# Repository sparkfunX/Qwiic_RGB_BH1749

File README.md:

SparkFun RGB Sensor (Qwiic) - BH1749NUC
========================================

[*SparkX RGB Sensor (Qwiic) - BH1749NUC (SPX-14733)*](https://www.sparkfun.com/products/14733)

Need to autonomously monitor for that specific color value? Want to hone in on that magenta ball? Or follow that aquamarine line? The BH1749NUC-based Qwiic RGB Sensor is here for all of your <span style="color:red">red</span>, <span style="color:green">green</span>, <span style="color:blue">blue</span>, and <span style="color:darkred">infrared</span> color-sensing needs.

The **BH1749NUC** features an I<sup>2</sup>C interface and a programmable interrupt output. It senses red, green, blue, and infrared in its field-of-view, then reports them as a 16-bit value. Additionally, it features programmable IR and RGB gains and a variable measurement rate. 

Also included on the breakout are individually-controllable white, red, green, and blue LEDs. The LEDs are managed with a **PCA9536** 4-channel I/O I<sup>2</sup>C expander. We've got a library for that too!

Check out the documents section for a pair of Arduino libraries -- for both the [BH1749NUC](https://github.com/sparkfun/SparkFun_BH1749NUC_Arduino_Library) and [PCA9536](https://github.com/sparkfun/SparkFun_PCA9536_Arduino_Library) IC's -- and a handful of examples to help get you started.

The Qwiic RGB Sensor uses our simple [Qwiic](https://www.sparkfun.com/qwiic) interface, so it requires no voltage translation and no figuring out which pin is SDA or SCL; just plug it in and go! As with any Qwiic board, this product includes a pair of Qwiic connectors to support a chain of multiple sensors.

SparkFun labored with love to create this code. Feel like supporting open source hardware? 
Buy a [breakout board](https://www.sparkfun.com/products/14733) from SparkFun!

Repository Contents
-------------------

* **/Documents** - Datasheets
* **/Hardware** - Eagle design files (.brd, .sch)

License Information
-------------------

This product is _**open source**_! 

If you have any questions or concerns on licensing, please contact techsupport@sparkfun.com.

Please use, reuse, and modify these files as you see fit. Please maintain attribution to SparkFun Electronics and release any derivative under the same license.

Distributed as-is; no warranty is given.

- Your friends at SparkFun.

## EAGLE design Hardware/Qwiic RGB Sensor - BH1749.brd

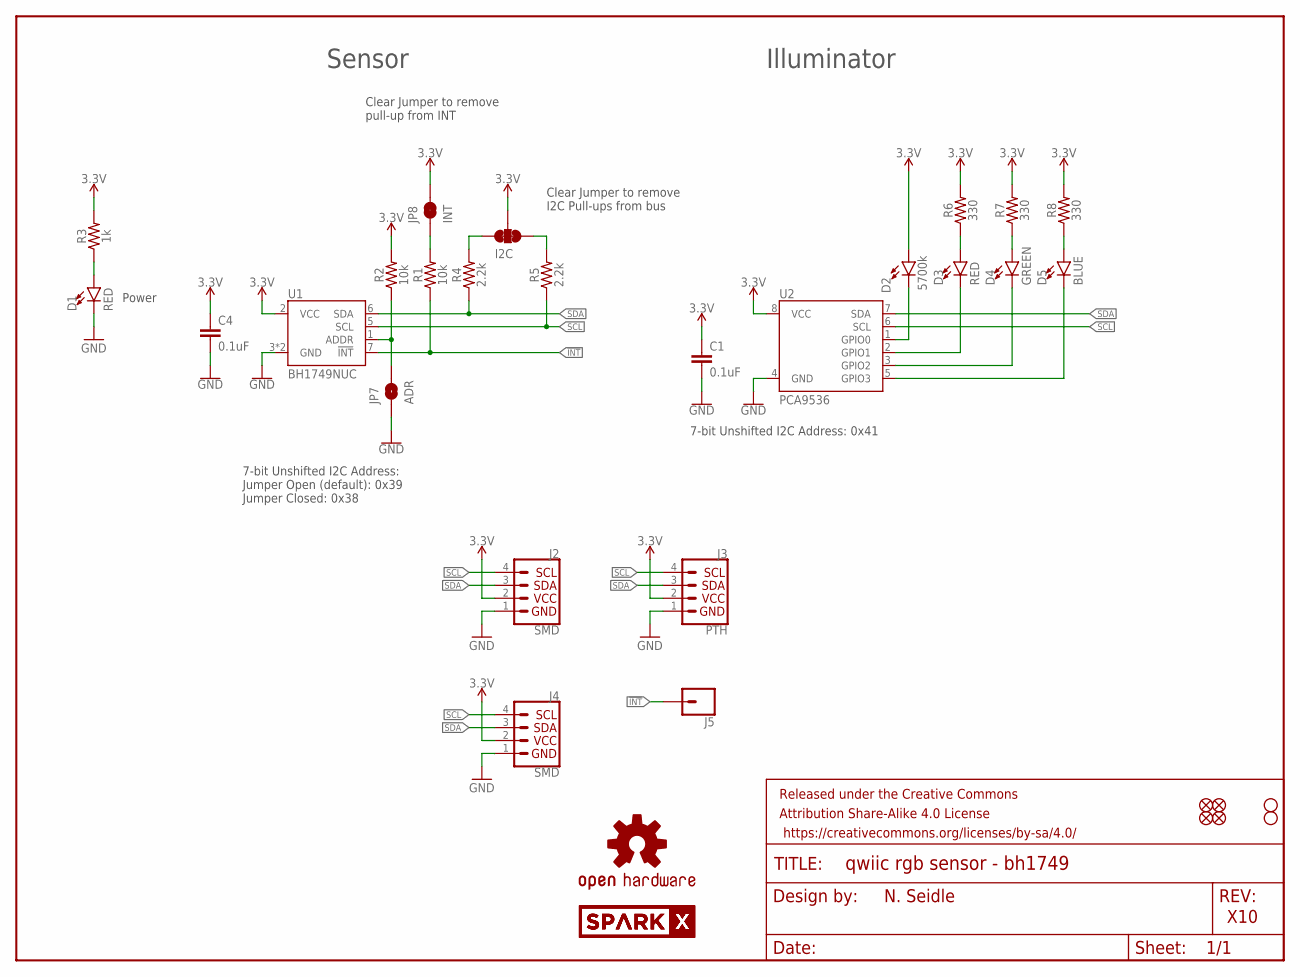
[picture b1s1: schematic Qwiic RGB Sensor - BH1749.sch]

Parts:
C1, C4: 0.1uF; 0603
D1, D3: RED; LED-0603
D2: 5700k; SUPER_BRIGHT_SMD_LED_1206
D4: GREEN; LED-0603
D5: BLUE; LED-0603
FRAME1: FRAME-LETTER; CREATIVE_COMMONS
I2C: JUMPER-SMT_3_2-NC_TRACE_SILK; SMT-JUMPER_3_2-NC_TRACE_SILK
J2, J4: SMD; 1X04_1MM_RA
J3: PTH; 1X04_NO_SILK
J5: CONN_01PTH_NO_SILK_YES_STOP; 1X01_NO_SILK
JP1, JP2, JP5, JP6: FIDUCIALUFIDUCIAL; MICRO-FIDUCIAL
JP3, JP4: STAND-OFF
JP7: ADR; SMT-JUMPER_2_NO_SILK
JP8: INT; SMT-JUMPER_2_NC_TRACE_SILK
LOGO1: OSHW-LOGOMINI; OSHW-LOGO-MINI
R1, R2: 10k; 0603
R3: 1k; 0603
R4, R5: 2.2k; 0603
R6, R7, R8: 330; 0603
U1: BH1749NUC
U2: PCA9536; MSOP8
U$1, U$2: SPARKX-LOGO4; SPARKX-MEDIUM

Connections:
3.3V: C1.1, C4.1, D2.A, I2C.2, J2.2 (VCC), J3.2 (VCC), J4.2 (VCC), JP8.2, R2.2, R3.2, R6.2, R7.2, R8.2, U1.2 (VCC), U2.8 (VCC)
!INT: J5.1, R1.1, U1.7 (!INT)
ADR: JP7.2, R2.1, U1.1 (ADDR)
GND: C1.2, C4.2, D1.C, J2.1 (GND), J3.1 (GND), J4.1 (GND), JP7.1, U1.3 (GND), U1.4 (GND), U2.4 (GND)
unnamed: I2C.1, R5.2
unnamed: I2C.3, R4.2
unnamed: D1.A, R3.1
unnamed: JP8.1, R1.2
unnamed: D3.C, U2.2 (GPIO1)
unnamed: D4.C, U2.3 (GPIO2)
unnamed: D5.C, U2.5 (GPIO3)
unnamed: D3.A, R6.1
unnamed: D4.A, R7.1
unnamed: D2.C, U2.1 (GPIO0)
unnamed: D5.A, R8.1
SCL: J2.4 (SCL), J3.4 (SCL), J4.4 (SCL), R5.1, U1.5 (SCL), U2.6 (SCL)
SDA: J2.3 (SDA), J3.3 (SDA), J4.3 (SDA), R4.1, U1.6 (SDA), U2.7 (SDA)

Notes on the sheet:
N. Seidle
X10
7-bit Unshifted I2C Address: Jumper Open (default): 0x39 Jumper Closed: 0x38
Clear Jumper to remove I2C Pull-ups from bus
Clear Jumper to remove pull-up from INT
Power
7-bit Unshifted I2C Address: 0x41
Sensor
Illuminator

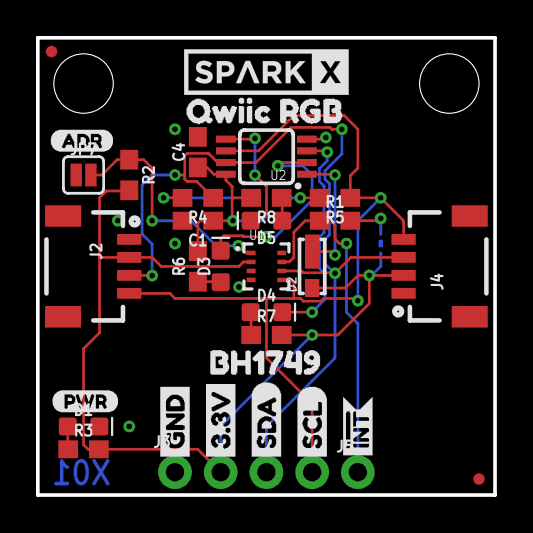
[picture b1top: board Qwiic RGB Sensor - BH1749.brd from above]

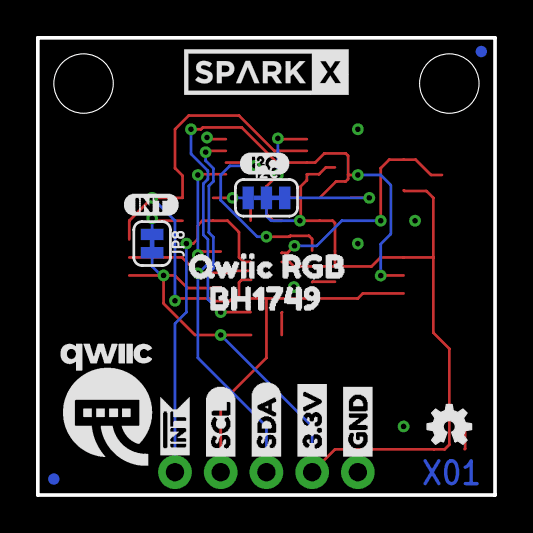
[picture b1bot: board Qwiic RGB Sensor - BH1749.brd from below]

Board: 2 copper layers, 25.4 x 25.4 mm, 53 parts (16 on the bottom side), 17 nets.

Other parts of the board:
U$3, U$22: GND1
U$4, U$21: 3#3V2
U$5, U$27: SDA8
U$6, U$26: SCL9
U$7, U$9: INT#-[<
U$8: QWIIC-LOGO-MEDIUM
U$10: I_SUPER2_C-()-03
U$11, U$13: BH17493
U$12, U$24: QWIIC_RGB2
U$16: PWR-()-03
U$17: ADR-()-03
U$20: INT0

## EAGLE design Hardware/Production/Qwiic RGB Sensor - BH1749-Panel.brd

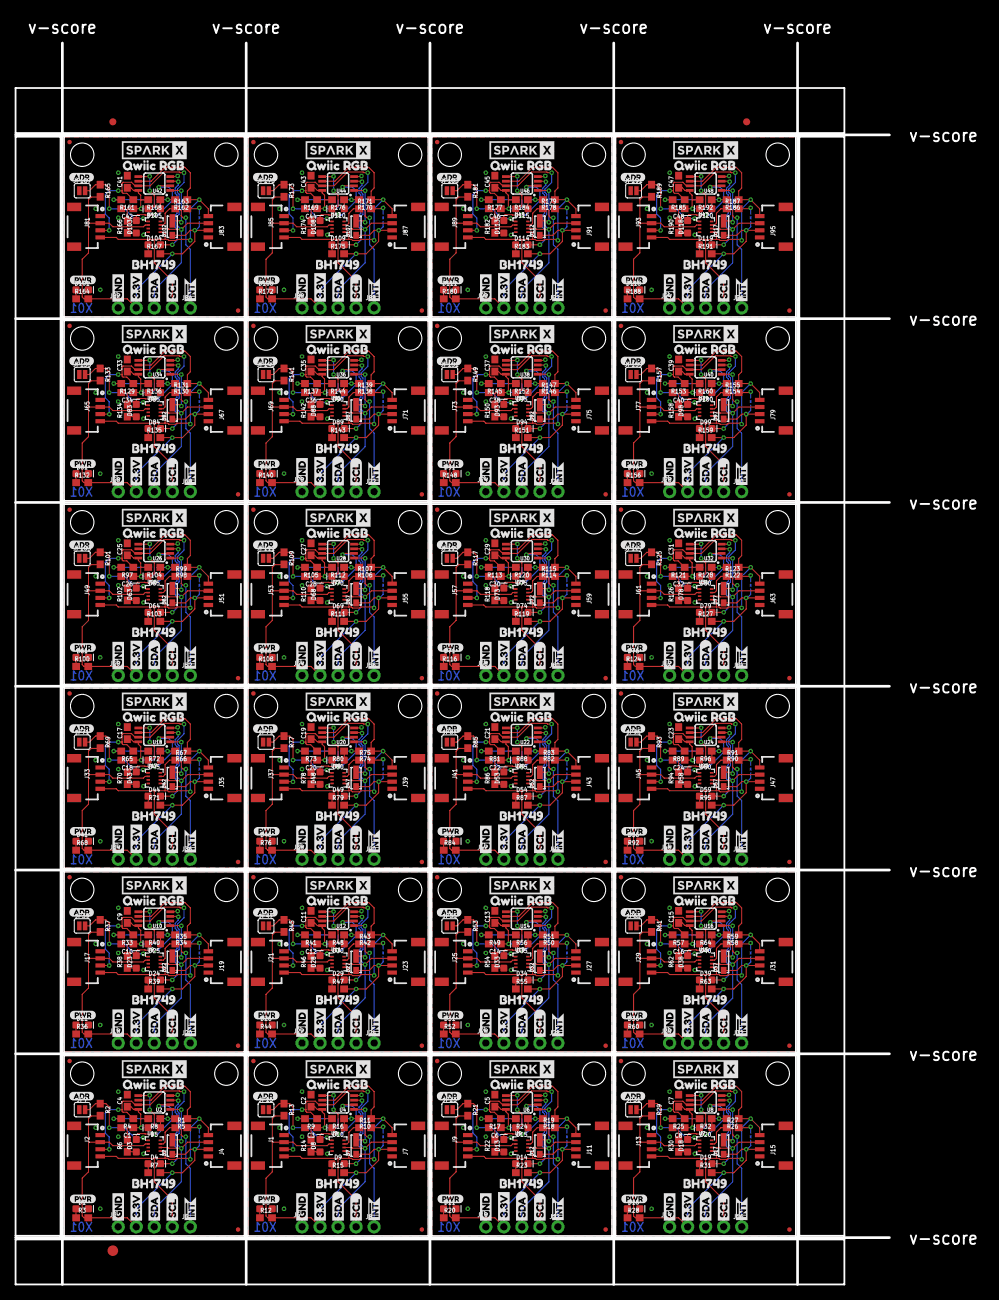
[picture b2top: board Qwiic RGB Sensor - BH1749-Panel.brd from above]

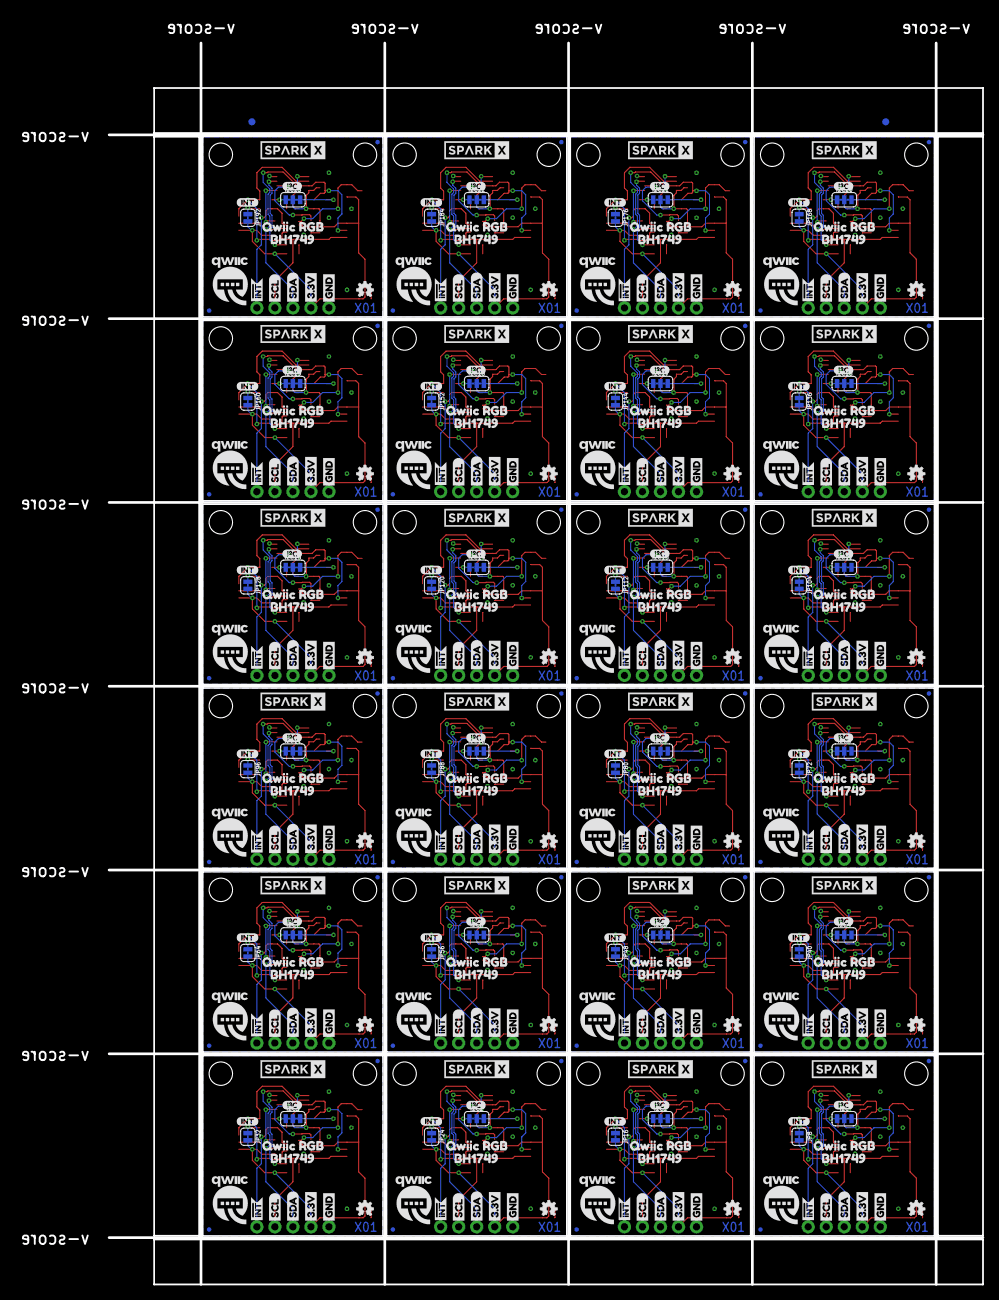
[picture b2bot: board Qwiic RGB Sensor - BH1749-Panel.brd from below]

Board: 2 copper layers, 123.2 x 175.0 mm, 1253 parts (386 on the bottom side), 408 nets.

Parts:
C1, C2, C3, C4, C5, C6, C7, C8, C9, C10, C11, C12, C13, C14, C15, C16, C17, C18, C19, C20, C21, C22, C23, C24, C25, C26, C27, C28, C29, C30, C31, C32, C33, C34, C35, C36, C37, C38, C39, C40, C41, C42, C43, C44, C45, C46, C47, C48: 0.1uF; 0603
D1, D3, D6, D8, D11, D13, D16, D18, D21, D23, D26, D28, D31, D33, D36, D38, D41, D43, D46, D48, D51, D53, D56, D58, D61, D63, D66, D68, D71, D73, D76, D78, D81, D83, D86, D88, D91, D93, D96, D98, D101, D103, D106, D108, D111, D113, D116, D118: RED; LED-0603
D2, D7, D12, D17, D22, D27, D32, D37, D42, D47, D52, D57, D62, D67, D72, D77, D82, D87, D92, D97, D102, D107, D112, D117: 5700k; SUPER_BRIGHT_SMD_LED_1206
D4, D9, D14, D19, D24, D29, D34, D39, D44, D49, D54, D59, D64, D69, D74, D79, D84, D89, D94, D99, D104, D109, D114, D119: GREEN; LED-0603
D5, D10, D15, D20, D25, D30, D35, D40, D45, D50, D55, D60, D65, D70, D75, D80, D85, D90, D95, D100, D105, D110, D115, D120: BLUE; LED-0603
E$1, E$2, E$3, E$4: FIDUCIAL-1X2
E$5: FIDUCIAL-1.5X3
I2C, I2C1, I2C2, I2C3, I2C4, I2C5, I2C6, I2C7, I2C8, I2C9, I2C10, I2C11, I2C12, I2C13, I2C14, I2C15, I2C16, I2C17, I2C18, I2C19, I2C20, I2C21, I2C22, I2C23: SMT-JUMPER_3_2-NC_TRACE_SILK
J1, J2, J4, J7, J9, J11, J13, J15, J17, J19, J21, J23, J25, J27, J29, J31, J33, J35, J37, J39, J41, J43, J45, J47, J49, J51, J53, J55, J57, J59, J61, J63, J65, J67, J69, J71, J73, J75, J77, J79, J81, J83, J85, J87, J89, J91, J93, J95: SMD; 1X04_1MM_RA
J3, J6, J10, J14, J18, J22, J26, J30, J34, J38, J42, J46, J50, J54, J58, J62, J66, J70, J74, J78, J82, J86, J90, J94: PTH; 1X04_NO_SILK
J5, J8, J12, J16, J20, J24, J28, J32, J36, J40, J44, J48, J52, J56, J60, J64, J68, J72, J76, J80, J84, J88, J92, J96: 1X01_NO_SILK
JP1, JP2, JP5, JP6, JP11, JP12, JP13, JP14, JP19, JP20, JP21, JP22, JP27, JP28, JP29, JP30, JP35, JP36, JP37, JP38, JP43, JP44, JP45, JP46, JP51, JP52, JP53, JP54, JP59, JP60, JP61, JP62, JP67, JP68, JP69, JP70, JP75, JP76, JP77, JP78, JP83, JP84, JP85, JP86, JP91, JP92, JP93, JP94, JP99, JP100, JP101, JP102, JP107, JP108, JP109, JP110, JP115, JP116, JP117, JP118, JP123, JP124, JP125, JP126, JP131, JP132, JP133, JP134, JP139, JP140, JP141, JP142, JP147, JP148, JP149, JP150, JP155, JP156, JP157, JP158, JP163, JP164, JP165, JP166, JP171, JP172, JP173, JP174, JP179, JP180, JP181, JP182, JP187, JP188, JP189, JP190: FIDUCIALUFIDUCIAL; MICRO-FIDUCIAL
JP3, JP4, JP9, JP10, JP17, JP18, JP25, JP26, JP33, JP34, JP41, JP42, JP49, JP50, JP57, JP58, JP65, JP66, JP73, JP74, JP81, JP82, JP89, JP90, JP97, JP98, JP105, JP106, JP113, JP114, JP121, JP122, JP129, JP130, JP137, JP138, JP145, JP146, JP153, JP154, JP161, JP162, JP169, JP170, JP177, JP178, JP185, JP186: STAND-OFF
JP7, JP15, JP23, JP31, JP39, JP47, JP55, JP63, JP71, JP79, JP87, JP95, JP103, JP111, JP119, JP127, JP135, JP143, JP151, JP159, JP167, JP175, JP183, JP191: ADR; SMT-JUMPER_2_NO_SILK
JP8, JP16, JP24, JP32, JP40, JP48, JP56, JP64, JP72, JP80, JP88, JP96, JP104, JP112, JP120, JP128, JP136, JP144, JP152, JP160, JP168, JP176, JP184, JP192: INT; SMT-JUMPER_2_NC_TRACE_SILK
LOGO1, LOGO2, LOGO3, LOGO4, LOGO5, LOGO6, LOGO7, LOGO8, LOGO9, LOGO10, LOGO11, LOGO12, LOGO13, LOGO14, LOGO15, LOGO16, LOGO17, LOGO18, LOGO19, LOGO20, LOGO21, LOGO22, LOGO23, LOGO24: OSHW-LOGOMINI; OSHW-LOGO-MINI
R1, R2, R11, R13, R19, R21, R27, R29, R35, R37, R43, R45, R51, R53, R59, R61, R67, R69, R75, R77, R83, R85, R91, R93, R99, R101, R107, R109, R115, R117, R123, R125, R131, R133, R139, R141, R147, R149, R155, R157, R163, R165, R171, R173, R179, R181, R187, R189: 10k; 0603
R3, R12, R20, R28, R36, R44, R52, R60, R68, R76, R84, R92, R100, R108, R116, R124, R132, R140, R148, R156, R164, R172, R180, R188: 1k; 0603
R4, R5, R9, R10, R17, R18, R25, R26, R33, R34, R41, R42, R49, R50, R57, R58, R65, R66, R73, R74, R81, R82, R89, R90, R97, R98, R105, R106, R113, R114, R121, R122, R129, R130, R137, R138, R145, R146, R153, R154, R161, R162, R169, R170, R177, R178, R185, R186: 2.2k; 0603
R6, R7, R8, R14, R15, R16, R22, R23, R24, R30, R31, R32, R38, R39, R40, R46, R47, R48, R54, R55, R56, R62, R63, R64, R70, R71, R72, R78, R79, R80, R86, R87, R88, R94, R95, R96, R102, R103, R104, R110, R111, R112, R118, R119, R120, R126, R127, R128, R134, R135, R136, R142, R143, R144, R150, R151, R152, R158, R159, R160, R166, R167, R168, R174, R175, R176, R182, R183, R184, R190, R191, R192: 330; 0603
U1, U3, U5, U7, U9, U11, U13, U15, U17, U19, U21, U23, U25, U27, U29, U31, U33, U35, U37, U39, U41, U43, U45, U47: BH1749NUC
U2, U4, U6, U8, U10, U12, U14, U16, U18, U20, U22, U24, U26, U28, U30, U32, U34, U36, U38, U40, U42, U44, U46, U48: PCA9536; MSOP8
U$1, U$2, U$14, U$15, U$43, U$44, U$64, U$65, U$85, U$86, U$106, U$107, U$127, U$128, U$148, U$149, U$169, U$170, U$190, U$191, U$211, U$212, U$232, U$233, U$253, U$254, U$274, U$275, U$295, U$296, U$316, U$317, U$337, U$338, U$358, U$359, U$379, U$380, U$400, U$401, U$421, U$422, U$442, U$443, U$463, U$464, U$484, U$485: SPARKX-LOGO4; SPARKX-MEDIUM
U$3, U$19, U$22, U$28, U$46, U$49, U$67, U$70, U$88, U$91, U$109, U$112, U$130, U$133, U$151, U$154, U$172, U$175, U$193, U$196, U$214, U$217, U$235, U$238, U$256, U$259, U$277, U$280, U$298, U$301, U$319, U$322, U$340, U$343, U$361, U$364, U$382, U$385, U$403, U$406, U$424, U$427, U$445, U$448, U$466, U$469, U$487, U$490: GND1
U$4, U$18, U$21, U$29, U$45, U$50, U$66, U$71, U$87, U$92, U$108, U$113, U$129, U$134, U$150, U$155, U$171, U$176, U$192, U$197, U$213, U$218, U$234, U$239, U$255, U$260, U$276, U$281, U$297, U$302, U$318, U$323, U$339, U$344, U$360, U$365, U$381, U$386, U$402, U$407, U$423, U$428, U$444, U$449, U$465, U$470, U$486, U$491: 3#3V2
U$5, U$25, U$27, U$30, U$48, U$51, U$69, U$72, U$90, U$93, U$111, U$114, U$132, U$135, U$153, U$156, U$174, U$177, U$195, U$198, U$216, U$219, U$237, U$240, U$258, U$261, U$279, U$282, U$300, U$303, U$321, U$324, U$342, U$345, U$363, U$366, U$384, U$387, U$405, U$408, U$426, U$429, U$447, U$450, U$468, U$471, U$489, U$492: SDA8
U$6, U$23, U$26, U$31, U$47, U$52, U$68, U$73, U$89, U$94, U$110, U$115, U$131, U$136, U$152, U$157, U$173, U$178, U$194, U$199, U$215, U$220, U$236, U$241, U$257, U$262, U$278, U$283, U$299, U$304, U$320, U$325, U$341, U$346, U$362, U$367, U$383, U$388, U$404, U$409, U$425, U$430, U$446, U$451, U$467, U$472, U$488, U$493: SCL9
U$7, U$9, U$33, U$34, U$54, U$55, U$75, U$76, U$96, U$97, U$117, U$118, U$138, U$139, U$159, U$160, U$180, U$181, U$201, U$202, U$222, U$223, U$243, U$244, U$264, U$265, U$285, U$286, U$306, U$307, U$327, U$328, U$348, U$349, U$369, U$370, U$390, U$391, U$411, U$412, U$432, U$433, U$453, U$454, U$474, U$475, U$495, U$496: INT#-[<
U$8, U$32, U$53, U$74, U$95, U$116, U$137, U$158, U$179, U$200, U$221, U$242, U$263, U$284, U$305, U$326, U$347, U$368, U$389, U$410, U$431, U$452, U$473, U$494: QWIIC-LOGO-MEDIUM
U$10, U$37, U$58, U$79, U$100, U$121, U$142, U$163, U$184, U$205, U$226, U$247, U$268, U$289, U$310, U$331, U$352, U$373, U$394, U$415, U$436, U$457, U$478, U$499: I_SUPER2_C-()-03
U$11, U$13, U$38, U$42, U$59, U$63, U$80, U$84, U$101, U$105, U$122, U$126, U$143, U$147, U$164, U$168, U$185, U$189, U$206, U$210, U$227, U$231, U$248, U$252, U$269, U$273, U$290, U$294, U$311, U$315, U$332, U$336, U$353, U$357, U$374, U$378, U$395, U$399, U$416, U$420, U$437, U$441, U$458, U$462, U$479, U$483, U$500, U$504: BH17493
U$12, U$24, U$40, U$41, U$61, U$62, U$82, U$83, U$103, U$104, U$124, U$125, U$145, U$146, U$166, U$167, U$187, U$188, U$208, U$209, U$229, U$230, U$250, U$251, U$271, U$272, U$292, U$293, U$313, U$314, U$334, U$335, U$355, U$356, U$376, U$377, U$397, U$398, U$418, U$419, U$439, U$440, U$460, U$461, U$481, U$482, U$502, U$503: QWIIC_RGB2
U$16, U$35, U$56, U$77, U$98, U$119, U$140, U$161, U$182, U$203, U$224, U$245, U$266, U$287, U$308, U$329, U$350, U$371, U$392, U$413, U$434, U$455, U$476, U$497: PWR-()-03
U$17, U$36, U$57, U$78, U$99, U$120, U$141, U$162, U$183, U$204, U$225, U$246, U$267, U$288, U$309, U$330, U$351, U$372, U$393, U$414, U$435, U$456, U$477, U$498: ADR-()-03
U$20, U$39, U$60, U$81, U$102, U$123, U$144, U$165, U$186, U$207, U$228, U$249, U$270, U$291, U$312, U$333, U$354, U$375, U$396, U$417, U$438, U$459, U$480, U$501: INT0

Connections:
3.3V: C1.1, C4.1, D2.A, I2C.2, J2.2, J3.2, J4.2, JP8.2, R2.2, R3.2, R6.2, R7.2, R8.2, U1.2, U2.8
3.3V1: C2.1, C3.1, D7.A, I2C1.2, J1.2, J6.2, J7.2, JP16.2, R12.2, R13.2, R14.2, R15.2, R16.2, U3.2, U4.8
3.3V2: C5.1, C6.1, D12.A, I2C2.2, J9.2, J10.2, J11.2, JP24.2, R20.2, R21.2, R22.2, R23.2, R24.2, U5.2, U6.8
3.3V3: C7.1, C8.1, D17.A, I2C3.2, J13.2, J14.2, J15.2, JP32.2, R28.2, R29.2, R30.2, R31.2, R32.2, U7.2, U8.8
3.3V4: C9.1, C10.1, D22.A, I2C4.2, J17.2, J18.2, J19.2, JP40.2, R36.2, R37.2, R38.2, R39.2, R40.2, U9.2, U10.8
3.3V5: C11.1, C12.1, D27.A, I2C5.2, J21.2, J22.2, J23.2, JP48.2, R44.2, R45.2, R46.2, R47.2, R48.2, U11.2, U12.8
3.3V6: C13.1, C14.1, D32.A, I2C6.2, J25.2, J26.2, J27.2, JP56.2, R52.2, R53.2, R54.2, R55.2, R56.2, U13.2, U14.8
3.3V7: C15.1, C16.1, D37.A, I2C7.2, J29.2, J30.2, J31.2, JP64.2, R60.2, R61.2, R62.2, R63.2, R64.2, U15.2, U16.8
3.3V8: C17.1, C18.1, D42.A, I2C8.2, J33.2, J34.2, J35.2, JP72.2, R68.2, R69.2, R70.2, R71.2, R72.2, U17.2, U18.8
3.3V9: C19.1, C20.1, D47.A, I2C9.2, J37.2, J38.2, J39.2, JP80.2, R76.2, R77.2, R78.2, R79.2, R80.2, U19.2, U20.8
3.3V10: C21.1, C22.1, D52.A, I2C10.2, J41.2, J42.2, J43.2, JP88.2, R84.2, R85.2, R86.2, R87.2, R88.2, U21.2, U22.8
3.3V11: C23.1, C24.1, D57.A, I2C11.2, J45.2, J46.2, J47.2, JP96.2, R92.2, R93.2, R94.2, R95.2, R96.2, U23.2, U24.8
3.3V12: C25.1, C26.1, D62.A, I2C12.2, J49.2, J50.2, J51.2, JP104.2, R100.2, R101.2, R102.2, R103.2, R104.2, U25.2, U26.8
3.3V13: C27.1, C28.1, D67.A, I2C13.2, J53.2, J54.2, J55.2, JP112.2, R108.2, R109.2, R110.2, R111.2, R112.2, U27.2, U28.8
3.3V14: C29.1, C30.1, D72.A, I2C14.2, J57.2, J58.2, J59.2, JP120.2, R116.2, R117.2, R118.2, R119.2, R120.2, U29.2, U30.8
3.3V15: C31.1, C32.1, D77.A, I2C15.2, J61.2, J62.2, J63.2, JP128.2, R124.2, R125.2, R126.2, R127.2, R128.2, U31.2, U32.8
3.3V16: C33.1, C34.1, D82.A, I2C16.2, J65.2, J66.2, J67.2, JP136.2, R132.2, R133.2, R134.2, R135.2, R136.2, U33.2, U34.8
3.3V17: C35.1, C36.1, D87.A, I2C17.2, J69.2, J70.2, J71.2, JP144.2, R140.2, R141.2, R142.2, R143.2, R144.2, U35.2, U36.8
3.3V18: C37.1, C38.1, D92.A, I2C18.2, J73.2, J74.2, J75.2, JP152.2, R148.2, R149.2, R150.2, R151.2, R152.2, U37.2, U38.8
3.3V19: C39.1, C40.1, D97.A, I2C19.2, J77.2, J78.2, J79.2, JP160.2, R156.2, R157.2, R158.2, R159.2, R160.2, U39.2, U40.8
3.3V20: C41.1, C42.1, D102.A, I2C20.2, J81.2, J82.2, J83.2, JP168.2, R164.2, R165.2, R166.2, R167.2, R168.2, U41.2, U42.8
3.3V21: C43.1, C44.1, D107.A, I2C21.2, J85.2, J86.2, J87.2, JP176.2, R172.2, R173.2, R174.2, R175.2, R176.2, U43.2, U44.8
3.3V22: C45.1, C46.1, D112.A, I2C22.2, J89.2, J90.2, J91.2, JP184.2, R180.2, R181.2, R182.2, R183.2, R184.2, U45.2, U46.8
3.3V23: C47.1, C48.1, D117.A, I2C23.2, J93.2, J94.2, J95.2, JP192.2, R188.2, R189.2, R190.2, R191.2, R192.2, U47.2, U48.8
!INT: J5.1, R1.1, U1.7
!INT1: J8.1, R11.1, U3.7
!INT2: J12.1, R19.1, U5.7
!INT3: J16.1, R27.1, U7.7
!INT4: J20.1, R35.1, U9.7
!INT5: J24.1, R43.1, U11.7
!INT6: J28.1, R51.1, U13.7
!INT7: J32.1, R59.1, U15.7
!INT8: J36.1, R67.1, U17.7
!INT9: J40.1, R75.1, U19.7
!INT10: J44.1, R83.1, U21.7
!INT11: J48.1, R91.1, U23.7
!INT12: J52.1, R99.1, U25.7
!INT13: J56.1, R107.1, U27.7
!INT14: J60.1, R115.1, U29.7
!INT15: J64.1, R123.1, U31.7
!INT16: J68.1, R131.1, U33.7
!INT17: J72.1, R139.1, U35.7
!INT18: J76.1, R147.1, U37.7
!INT19: J80.1, R155.1, U39.7
!INT20: J84.1, R163.1, U41.7
!INT21: J88.1, R171.1, U43.7
!INT22: J92.1, R179.1, U45.7
!INT23: J96.1, R187.1, U47.7
ADR: JP7.2, R2.1, U1.1
ADR1: JP15.2, R13.1, U3.1
ADR2: JP23.2, R21.1, U5.1
ADR3: JP31.2, R29.1, U7.1
ADR4: JP39.2, R37.1, U9.1
ADR5: JP47.2, R45.1, U11.1
ADR6: JP55.2, R53.1, U13.1
ADR7: JP63.2, R61.1, U15.1
ADR8: JP71.2, R69.1, U17.1
ADR9: JP79.2, R77.1, U19.1
ADR10: JP87.2, R85.1, U21.1
ADR11: JP95.2, R93.1, U23.1
ADR12: JP103.2, R101.1, U25.1
ADR13: JP111.2, R109.1, U27.1
ADR14: JP119.2, R117.1, U29.1
ADR15: JP127.2, R125.1, U31.1
ADR16: JP135.2, R133.1, U33.1
ADR17: JP143.2, R141.1, U35.1
ADR18: JP151.2, R149.1, U37.1
ADR19: JP159.2, R157.1, U39.1
ADR20: JP167.2, R165.1, U41.1
ADR21: JP175.2, R173.1, U43.1
ADR22: JP183.2, R181.1, U45.1
ADR23: JP191.2, R189.1, U47.1
GND: C1.2, C4.2, D1.C, J2.1, J3.1, J4.1, JP7.1, U1.3, U1.4, U2.4
GND1: C2.2, C3.2, D6.C, J1.1, J6.1, J7.1, JP15.1, U3.3, U3.4, U4.4
GND2: C5.2, C6.2, D11.C, J9.1, J10.1, J11.1, JP23.1, U5.3, U5.4, U6.4
GND3: C7.2, C8.2, D16.C, J13.1, J14.1, J15.1, JP31.1, U7.3, U7.4, U8.4
GND4: C9.2, C10.2, D21.C, J17.1, J18.1, J19.1, JP39.1, U9.3, U9.4, U10.4
GND5: C11.2, C12.2, D26.C, J21.1, J22.1, J23.1, JP47.1, U11.3, U11.4, U12.4
GND6: C13.2, C14.2, D31.C, J25.1, J26.1, J27.1, JP55.1, U13.3, U13.4, U14.4
GND7: C15.2, C16.2, D36.C, J29.1, J30.1, J31.1, JP63.1, U15.3, U15.4, U16.4
GND8: C17.2, C18.2, D41.C, J33.1, J34.1, J35.1, JP71.1, U17.3, U17.4, U18.4
GND9: C19.2, C20.2, D46.C, J37.1, J38.1, J39.1, JP79.1, U19.3, U19.4, U20.4
GND10: C21.2, C22.2, D51.C, J41.1, J42.1, J43.1, JP87.1, U21.3, U21.4, U22.4
GND11: C23.2, C24.2, D56.C, J45.1, J46.1, J47.1, JP95.1, U23.3, U23.4, U24.4
GND12: C25.2, C26.2, D61.C, J49.1, J50.1, J51.1, JP103.1, U25.3, U25.4, U26.4
GND13: C27.2, C28.2, D66.C, J53.1, J54.1, J55.1, JP111.1, U27.3, U27.4, U28.4
GND14: C29.2, C30.2, D71.C, J57.1, J58.1, J59.1, JP119.1, U29.3, U29.4, U30.4
GND15: C31.2, C32.2, D76.C, J61.1, J62.1, J63.1, JP127.1, U31.3, U31.4, U32.4
GND16: C33.2, C34.2, D81.C, J65.1, J66.1, J67.1, JP135.1, U33.3, U33.4, U34.4
GND17: C35.2, C36.2, D86.C, J69.1, J70.1, J71.1, JP143.1, U35.3, U35.4, U36.4
GND18: C37.2, C38.2, D91.C, J73.1, J74.1, J75.1, JP151.1, U37.3, U37.4, U38.4
GND19: C39.2, C40.2, D96.C, J77.1, J78.1, J79.1, JP159.1, U39.3, U39.4, U40.4
GND20: C41.2, C42.2, D101.C, J81.1, J82.1, J83.1, JP167.1, U41.3, U41.4, U42.4
GND21: C43.2, C44.2, D106.C, J85.1, J86.1, J87.1, JP175.1, U43.3, U43.4, U44.4
GND22: C45.2, C46.2, D111.C, J89.1, J90.1, J91.1, JP183.1, U45.3, U45.4, U46.4
GND23: C47.2, C48.2, D116.C, J93.1, J94.1, J95.1, JP191.1, U47.3, U47.4, U48.4
unnamed: I2C.1, R5.2
unnamed: I2C.3, R4.2
unnamed: D1.A, R3.1
unnamed: JP8.1, R1.2
unnamed: D3.C, U2.2
unnamed: D4.C, U2.3
unnamed: D5.C, U2.5
unnamed: D3.A, R6.1
unnamed: D4.A, R7.1
unnamed: D2.C, U2.1
unnamed: D5.A, R8.1
unnamed: I2C1.1, R10.2
unnamed: I2C1.3, R9.2
unnamed: JP16.1, R11.2
unnamed: D6.A, R12.1
unnamed: D7.C, U4.1
unnamed: D8.C, U4.2
unnamed: D9.C, U4.3
unnamed: D10.C, U4.5
unnamed: D8.A, R14.1
unnamed: D9.A, R15.1
unnamed: D10.A, R16.1
unnamed: I2C2.1, R18.2
unnamed: I2C2.3, R17.2
unnamed: JP24.1, R19.2
unnamed: D11.A, R20.1
unnamed: D12.C, U6.1
unnamed: D13.C, U6.2
unnamed: D14.C, U6.3
unnamed: D15.C, U6.5
unnamed: D13.A, R22.1
unnamed: D14.A, R23.1
unnamed: D15.A, R24.1
unnamed: I2C3.1, R26.2
unnamed: I2C3.3, R25.2
unnamed: JP32.1, R27.2
unnamed: D16.A, R28.1
unnamed: D17.C, U8.1
unnamed: D18.C, U8.2
unnamed: D19.C, U8.3
unnamed: D20.C, U8.5
unnamed: D18.A, R30.1
unnamed: D19.A, R31.1
unnamed: D20.A, R32.1
unnamed: I2C4.1, R34.2
unnamed: I2C4.3, R33.2
unnamed: JP40.1, R35.2
unnamed: D21.A, R36.1
unnamed: D22.C, U10.1
unnamed: D23.C, U10.2
unnamed: D24.C, U10.3
unnamed: D25.C, U10.5
unnamed: D23.A, R38.1
unnamed: D24.A, R39.1
unnamed: D25.A, R40.1
unnamed: I2C5.1, R42.2
unnamed: I2C5.3, R41.2
unnamed: JP48.1, R43.2
unnamed: D26.A, R44.1
unnamed: D27.C, U12.1
unnamed: D28.C, U12.2
unnamed: D29.C, U12.3
unnamed: D30.C, U12.5
unnamed: D28.A, R46.1
unnamed: D29.A, R47.1
unnamed: D30.A, R48.1
unnamed: I2C6.1, R50.2
unnamed: I2C6.3, R49.2
unnamed: JP56.1, R51.2
unnamed: D31.A, R52.1
unnamed: D32.C, U14.1
unnamed: D33.C, U14.2
unnamed: D34.C, U14.3
unnamed: D35.C, U14.5
unnamed: D33.A, R54.1
unnamed: D34.A, R55.1
unnamed: D35.A, R56.1
unnamed: I2C7.1, R58.2
unnamed: I2C7.3, R57.2
unnamed: JP64.1, R59.2
unnamed: D36.A, R60.1
unnamed: D37.C, U16.1
unnamed: D38.C, U16.2
unnamed: D39.C, U16.3
unnamed: D40.C, U16.5
unnamed: D38.A, R62.1
unnamed: D39.A, R63.1
unnamed: D40.A, R64.1
unnamed: I2C8.1, R66.2
unnamed: I2C8.3, R65.2
unnamed: JP72.1, R67.2
unnamed: D41.A, R68.1
unnamed: D42.C, U18.1
unnamed: D43.C, U18.2
unnamed: D44.C, U18.3
unnamed: D45.C, U18.5
unnamed: D43.A, R70.1
unnamed: D44.A, R71.1
unnamed: D45.A, R72.1
unnamed: I2C9.1, R74.2
unnamed: I2C9.3, R73.2
unnamed: JP80.1, R75.2
unnamed: D46.A, R76.1
unnamed: D47.C, U20.1
unnamed: D48.C, U20.2
unnamed: D49.C, U20.3
unnamed: D50.C, U20.5
unnamed: D48.A, R78.1
unnamed: D49.A, R79.1
unnamed: D50.A, R80.1
unnamed: I2C10.1, R82.2
unnamed: I2C10.3, R81.2
unnamed: JP88.1, R83.2
unnamed: D51.A, R84.1
unnamed: D52.C, U22.1
unnamed: D53.C, U22.2
unnamed: D54.C, U22.3
unnamed: D55.C, U22.5
unnamed: D53.A, R86.1
unnamed: D54.A, R87.1
unnamed: D55.A, R88.1
unnamed: I2C11.1, R90.2
unnamed: I2C11.3, R89.2
unnamed: JP96.1, R91.2
unnamed: D56.A, R92.1
unnamed: D57.C, U24.1
unnamed: D58.C, U24.2
unnamed: D59.C, U24.3
unnamed: D60.C, U24.5
unnamed: D58.A, R94.1
unnamed: D59.A, R95.1
unnamed: D60.A, R96.1
unnamed: I2C12.1, R98.2
unnamed: I2C12.3, R97.2
unnamed: JP104.1, R99.2
unnamed: D61.A, R100.1
unnamed: D62.C, U26.1
unnamed: D63.C, U26.2
unnamed: D64.C, U26.3
unnamed: D65.C, U26.5
unnamed: D63.A, R102.1
unnamed: D64.A, R103.1
unnamed: D65.A, R104.1
unnamed: I2C13.1, R106.2
unnamed: I2C13.3, R105.2
unnamed: JP112.1, R107.2
unnamed: D66.A, R108.1
unnamed: D67.C, U28.1
unnamed: D68.C, U28.2
unnamed: D69.C, U28.3
unnamed: D70.C, U28.5
unnamed: D68.A, R110.1
unnamed: D69.A, R111.1
unnamed: D70.A, R112.1
unnamed: I2C14.1, R114.2
unnamed: I2C14.3, R113.2
unnamed: JP120.1, R115.2
unnamed: D71.A, R116.1
unnamed: D72.C, U30.1
unnamed: D73.C, U30.2
unnamed: D74.C, U30.3
unnamed: D75.C, U30.5
unnamed: D73.A, R118.1
unnamed: D74.A, R119.1
unnamed: D75.A, R120.1
unnamed: I2C15.1, R122.2
unnamed: I2C15.3, R121.2
unnamed: JP128.1, R123.2
unnamed: D76.A, R124.1
unnamed: D77.C, U32.1
unnamed: D78.C, U32.2
unnamed: D79.C, U32.3
unnamed: D80.C, U32.5
unnamed: D78.A, R126.1
unnamed: D79.A, R127.1
unnamed: D80.A, R128.1
unnamed: I2C16.1, R130.2
unnamed: I2C16.3, R129.2
unnamed: JP136.1, R131.2
unnamed: D81.A, R132.1
unnamed: D82.C, U34.1
unnamed: D83.C, U34.2
unnamed: D84.C, U34.3
unnamed: D85.C, U34.5
unnamed: D83.A, R134.1
unnamed: D84.A, R135.1
unnamed: D85.A, R136.1
unnamed: I2C17.1, R138.2
unnamed: I2C17.3, R137.2
unnamed: JP144.1, R139.2
unnamed: D86.A, R140.1
unnamed: D87.C, U36.1
unnamed: D88.C, U36.2
unnamed: D89.C, U36.3
unnamed: D90.C, U36.5
unnamed: D88.A, R142.1
unnamed: D89.A, R143.1
unnamed: D90.A, R144.1
unnamed: I2C18.1, R146.2
unnamed: I2C18.3, R145.2
unnamed: JP152.1, R147.2
unnamed: D91.A, R148.1
unnamed: D92.C, U38.1
unnamed: D93.C, U38.2
unnamed: D94.C, U38.3
unnamed: D95.C, U38.5
unnamed: D93.A, R150.1
unnamed: D94.A, R151.1
unnamed: D95.A, R152.1
unnamed: I2C19.1, R154.2
unnamed: I2C19.3, R153.2
unnamed: JP160.1, R155.2
unnamed: D96.A, R156.1
unnamed: D97.C, U40.1
unnamed: D98.C, U40.2
unnamed: D99.C, U40.3
unnamed: D100.C, U40.5
unnamed: D98.A, R158.1
unnamed: D99.A, R159.1
unnamed: D100.A, R160.1
unnamed: I2C20.1, R162.2
unnamed: I2C20.3, R161.2
unnamed: JP168.1, R163.2
unnamed: D101.A, R164.1
unnamed: D102.C, U42.1
unnamed: D103.C, U42.2
unnamed: D104.C, U42.3
unnamed: D105.C, U42.5
unnamed: D103.A, R166.1
unnamed: D104.A, R167.1
unnamed: D105.A, R168.1
unnamed: I2C21.1, R170.2
unnamed: I2C21.3, R169.2
unnamed: JP176.1, R171.2
unnamed: D106.A, R172.1
unnamed: D107.C, U44.1
unnamed: D108.C, U44.2
unnamed: D109.C, U44.3
unnamed: D110.C, U44.5
unnamed: D108.A, R174.1
unnamed: D109.A, R175.1
unnamed: D110.A, R176.1
unnamed: I2C22.1, R178.2
unnamed: I2C22.3, R177.2
unnamed: JP184.1, R179.2
unnamed: D111.A, R180.1
unnamed: D112.C, U46.1
unnamed: D113.C, U46.2
unnamed: D114.C, U46.3
unnamed: D115.C, U46.5
unnamed: D113.A, R182.1
unnamed: D114.A, R183.1
unnamed: D115.A, R184.1
unnamed: I2C23.1, R186.2
unnamed: I2C23.3, R185.2
unnamed: JP192.1, R187.2
unnamed: D116.A, R188.1
unnamed: D117.C, U48.1
unnamed: D118.C, U48.2
unnamed: D119.C, U48.3
unnamed: D120.C, U48.5
unnamed: D118.A, R190.1
unnamed: D119.A, R191.1
unnamed: D120.A, R192.1
SCL: J2.4, J3.4, J4.4, R5.1, U1.5, U2.6
SCL1: J1.4, J6.4, J7.4, R10.1, U3.5, U4.6
SCL2: J9.4, J10.4, J11.4, R18.1, U5.5, U6.6
SCL3: J13.4, J14.4, J15.4, R26.1, U7.5, U8.6
SCL4: J17.4, J18.4, J19.4, R34.1, U9.5, U10.6
SCL5: J21.4, J22.4, J23.4, R42.1, U11.5, U12.6
SCL6: J25.4, J26.4, J27.4, R50.1, U13.5, U14.6
SCL7: J29.4, J30.4, J31.4, R58.1, U15.5, U16.6
SCL8: J33.4, J34.4, J35.4, R66.1, U17.5, U18.6
SCL9: J37.4, J38.4, J39.4, R74.1, U19.5, U20.6
SCL10: J41.4, J42.4, J43.4, R82.1, U21.5, U22.6
SCL11: J45.4, J46.4, J47.4, R90.1, U23.5, U24.6
SCL12: J49.4, J50.4, J51.4, R98.1, U25.5, U26.6
SCL13: J53.4, J54.4, J55.4, R106.1, U27.5, U28.6
SCL14: J57.4, J58.4, J59.4, R114.1, U29.5, U30.6
SCL15: J61.4, J62.4, J63.4, R122.1, U31.5, U32.6
SCL16: J65.4, J66.4, J67.4, R130.1, U33.5, U34.6
SCL17: J69.4, J70.4, J71.4, R138.1, U35.5, U36.6
SCL18: J73.4, J74.4, J75.4, R146.1, U37.5, U38.6
SCL19: J77.4, J78.4, J79.4, R154.1, U39.5, U40.6
SCL20: J81.4, J82.4, J83.4, R162.1, U41.5, U42.6
SCL21: J85.4, J86.4, J87.4, R170.1, U43.5, U44.6
SCL22: J89.4, J90.4, J91.4, R178.1, U45.5, U46.6
SCL23: J93.4, J94.4, J95.4, R186.1, U47.5, U48.6
SDA: J2.3, J3.3, J4.3, R4.1, U1.6, U2.7
SDA1: J1.3, J6.3, J7.3, R9.1, U3.6, U4.7
SDA2: J9.3, J10.3, J11.3, R17.1, U5.6, U6.7
SDA3: J13.3, J14.3, J15.3, R25.1, U7.6, U8.7
SDA4: J17.3, J18.3, J19.3, R33.1, U9.6, U10.7
SDA5: J21.3, J22.3, J23.3, R41.1, U11.6, U12.7
SDA6: J25.3, J26.3, J27.3, R49.1, U13.6, U14.7
SDA7: J29.3, J30.3, J31.3, R57.1, U15.6, U16.7
SDA8: J33.3, J34.3, J35.3, R65.1, U17.6, U18.7
SDA9: J37.3, J38.3, J39.3, R73.1, U19.6, U20.7
SDA10: J41.3, J42.3, J43.3, R81.1, U21.6, U22.7
SDA11: J45.3, J46.3, J47.3, R89.1, U23.6, U24.7
SDA12: J49.3, J50.3, J51.3, R97.1, U25.6, U26.7
SDA13: J53.3, J54.3, J55.3, R105.1, U27.6, U28.7
SDA14: J57.3, J58.3, J59.3, R113.1, U29.6, U30.7
SDA15: J61.3, J62.3, J63.3, R121.1, U31.6, U32.7
SDA16: J65.3, J66.3, J67.3, R129.1, U33.6, U34.7
SDA17: J69.3, J70.3, J71.3, R137.1, U35.6, U36.7
SDA18: J73.3, J74.3, J75.3, R145.1, U37.6, U38.7
SDA19: J77.3, J78.3, J79.3, R153.1, U39.6, U40.7
SDA20: J81.3, J82.3, J83.3, R161.1, U41.6, U42.7
SDA21: J85.3, J86.3, J87.3, R169.1, U43.6, U44.7
SDA22: J89.3, J90.3, J91.3, R177.1, U45.6, U46.7
SDA23: J93.3, J94.3, J95.3, R185.1, U47.6, U48.7

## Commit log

2018-05-10 Adding README.md
2020-03-25 Adding larger panel.

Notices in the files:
parts and their libraries:
SparkFun-Resistors: Licensing: Creative Commons ShareAlike 4.0 International - https://creativecommons.org/licenses/by-sa/4.0
SparkFun-Aesthetics: Released under the Creative Commons Attribution Share-Alike 4.0 License
SparkFun-Aesthetics: https://creativecommons.org/licenses/by-sa/4.0
